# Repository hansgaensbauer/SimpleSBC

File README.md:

# SimpleSBC
A simple, open source SBC built around the STM32MP1

## Getting Started
1. `git clone` this repository
2. Run `git submodule init` and `git submodule update --recursive` to get Yocto and layers
3. Install dependencies:
   ```
   sudo apt update
   sudo apt upgrade
   sudo apt install -y bc build-essential chrpath cpio diffstat gawk git texinfo wget gdisk python3 python3-pip
   ```
4. Run `source yocto/poky/oe-init-build-env build-simplesbc` to set up the environment
5. Run `bitbake custom-image` to build! This could take a while
6. After the build, use yocto\copy_sd.sh to set up an SD card. You may need to change the device name in the script.
7. Connect an ST-Link or other USB-Serial converter, and plug in power.
8. Enjoy linux! The default meta-custom layer includes python and some python libraries. 

## Related Projects
- [Linux-Keyer](https://github.com/hansgaensbauer/Linux-Keyer/tree/main): A real-time linux based CW keyer built around SimpleSBC

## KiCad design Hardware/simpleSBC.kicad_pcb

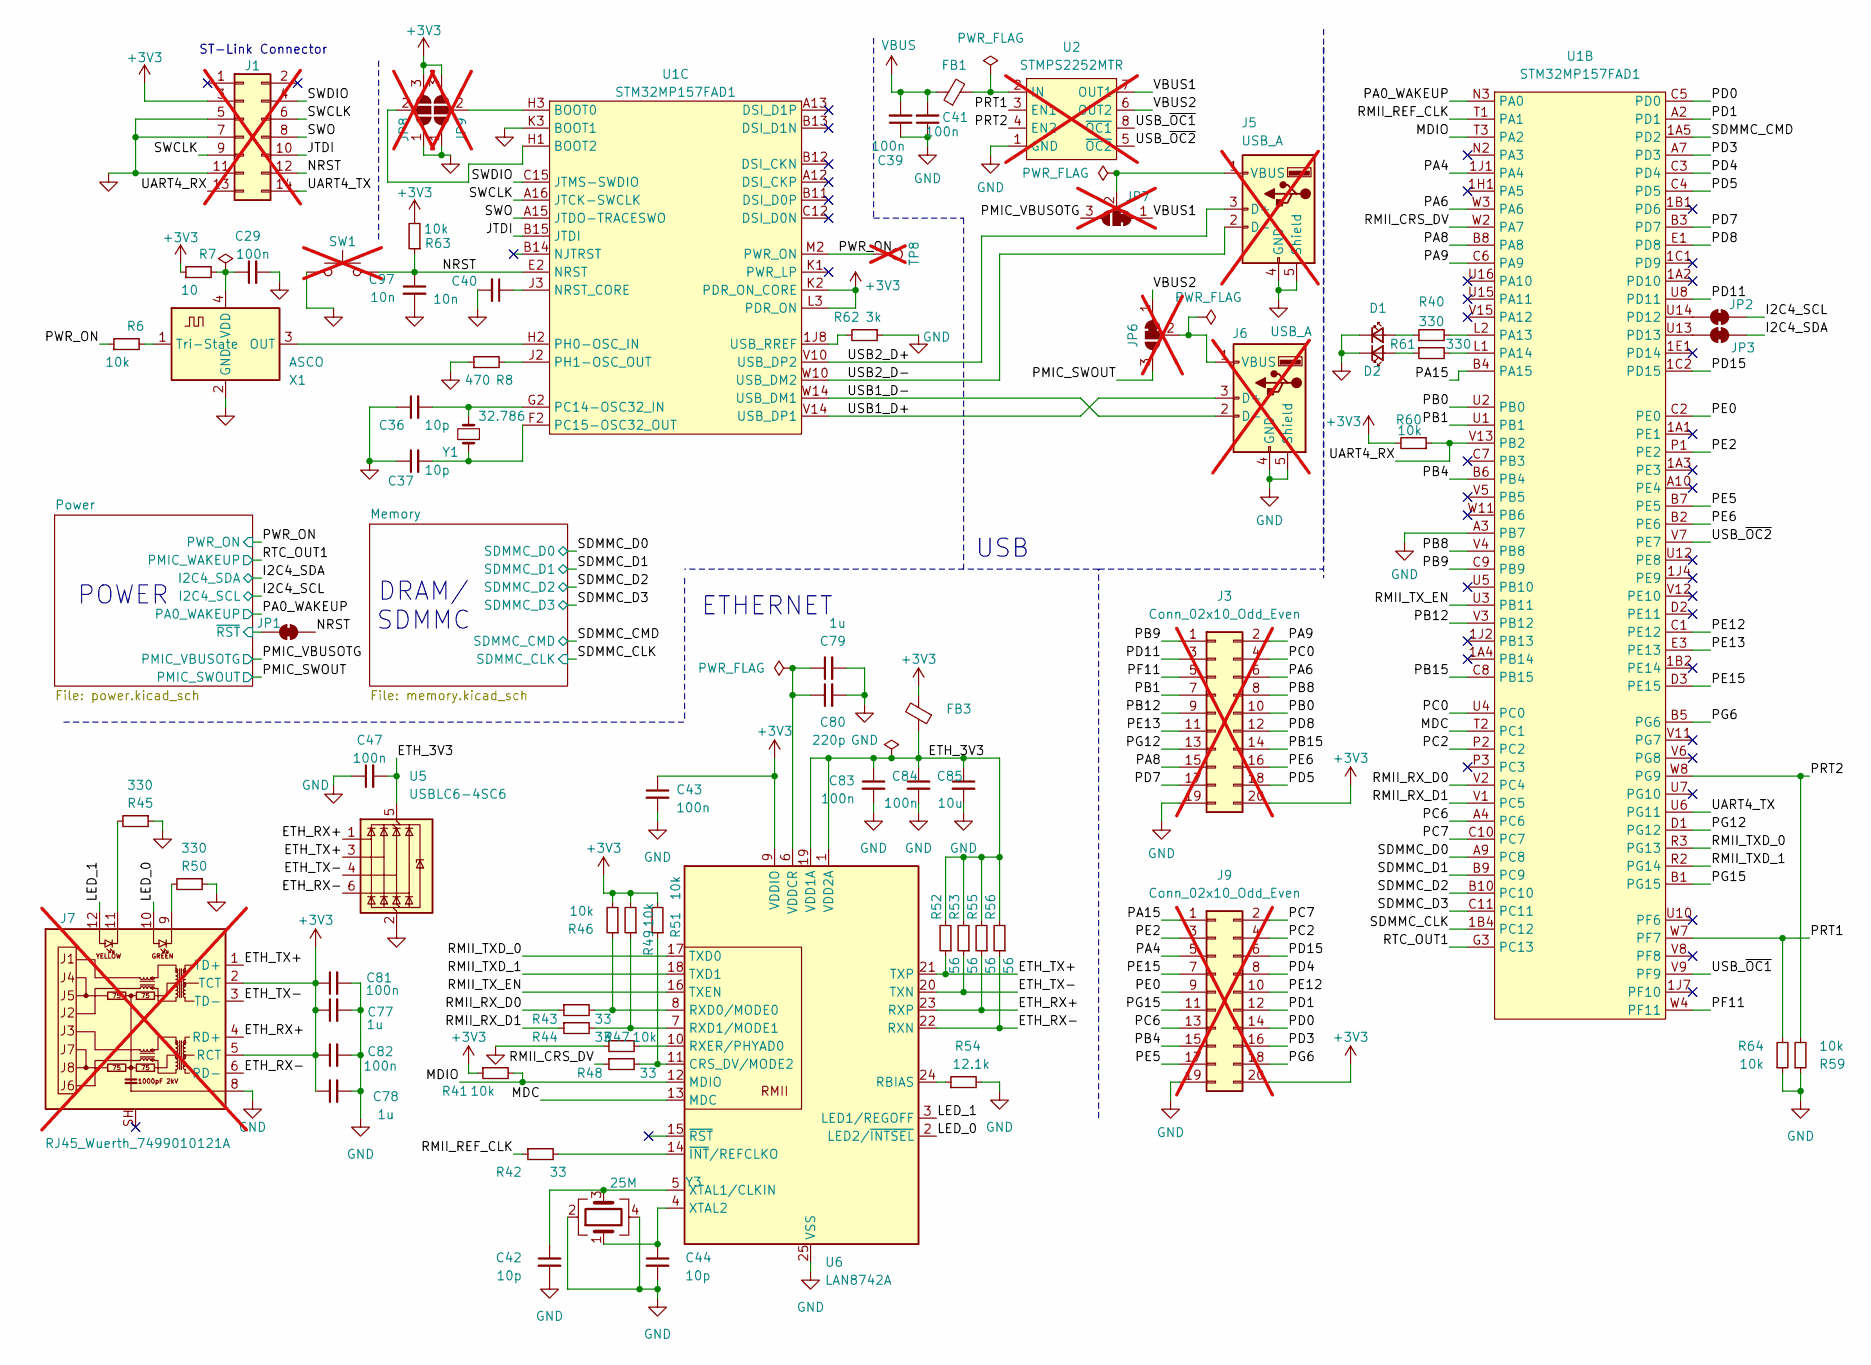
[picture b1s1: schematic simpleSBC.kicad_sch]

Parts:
C29, C39, C41, C43, C47, C81, C82, C83, C84: 100n; C_0402_1005Metric; JLCPCB Part # C1525
C36, C37, C42, C44: 10p; C_0402_1005Metric; JLCPCB Part # C32949
C40, C97: 10n; C_0402_1005Metric; JLCPCB Part # C15195
C77, C78, C79: 1u; C_0402_1005Metric; JLCPCB Part # C52923
C80: 220p; C_0402_1005Metric; JLCPCB Part # C1530
C85: 10u; C_0805_2012Metric; JLCPCB Part # C15850
D1: LED_Small; LED_0805_2012Metric; JLCPCB Part # C2296
D2: LED_Small; LED_0805_2012Metric; JLCPCB Part # C2297
FB1, FB3: FerriteBead_Small; L_0603_1608Metric; JLCPCB Part # C1002
J1: Conn_02x07_Odd_Even; PinHeader_2x7_P1.27mm_SMD; not fitted
J3, J9: Conn_02x10_Odd_Even; PinHeader_2x10_P2.54mm_Vertical; not fitted
J5, J6: USB_A; USB_A_Molex_67643_Horizontal; not fitted
J7: RJ45_Wuerth_7499010121A; RJ45_Wuerth_7499010121A_Horizontal; not fitted
JP1, JP2, JP3: SolderJumper_2_Bridged; Jumper_0402_Short
JP6, JP7: SolderJumper_3_Bridged12; SolderJumper-3_P1.3mm_Bridged2Bar12_Pad1.0x1.5mm; not fitted
JP8, JP9: SolderJumper_3_Open; SolderJumper-3_P1.3mm_Open_Pad1.0x1.5mm; not fitted
R6, R41, R46, R47, R49, R51, R59, R60, R63, R64: 10k; R_0402_1005Metric; JLCPCB Part # C25744
R7: 10; R_0402_1005Metric; JLCPCB Part # C25077
R8: 470; R_0402_1005Metric; JLCPCB Part # C25117
R40, R45, R50, R61: 330; R_0402_1005Metric; JLCPCB Part # C25104
R42, R43, R44, R48: 33; R_0402_1005Metric; JLCPCB Part # C25105
R52, R53, R55, R56: 56; R_0402_1005Metric; JLCPCB Part # C25127
R54: 12.1k; R_0402_1005Metric; JLCPCB Part # C25863
R62: 3k; R_0402_1005Metric; JLCPCB Part # C881171
SW1: SW_Push; SW_SPST_Omron_B3FS-101xP; not fitted
TP8: TestPoint; TestPoint_Pad_D1.0mm; not fitted
U1: STM32MP157FAD1; TFBGA257; JLCPCB Part # C1236719
U2: STMPS2252MTR; SOIC-8_3.9x4.9mm_P1.27mm; JLCPCB Part # C2680426; not fitted
U5: USBLC6-4SC6; SOT-23-6; JLCPCB Part # C111212
U6: LAN8742A; VQFN-24-1EP_4x4mm_P0.5mm_EP2.5x2.5mm_ThermalVias; JLCPCB Part # C220794
X1: ASCO; Oscillator_SMD_Abracon_ASCO-4Pin_1.6x1.2mm; JLCPCB Part # C19078199
Y1: 32.786; Crystal_SMD_MicroCrystal_CM9V-T1A-2Pin_1.6x1.0mm; JLCPCB Part # C5341287
Y3: 25M; Crystal_2.00x1.60mm; MPN 402F2501XIAR; JLCPCB Part # C127895

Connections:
+3V3: C43.1, C77.1, C78.1, C81.1, C82.1, FB3.2, J1.3, J3.20, J7.2 (TCT), J7.5 (RCT), J9.20, JP8.3 (B), JP9.3 (B), R7.1, R41.1, R46.2, R49.2, R51.2, R60.2, R63.2, U1.K2 (PDR_ON_CORE), U1.L3 (PDR_ON), U6.9 (VDDIO); also elsewhere on the board
/ETH_3V3: C47.2, C83.1, C84.1, C85.1, FB3.1, R52.2, R53.2, R55.2, R56.2, U5.5 (VBUS), U6.1 (VDD2A), U6.19 (VDD1A)
/ETH_RX+: J7.4 (RD+), R55.1, U5.1 (I/O1), U6.23 (RXP)
/ETH_RX-: J7.6 (RD-), R56.1, U5.6 (I/O4), U6.22 (RXN)
/ETH_TX+: J7.1 (TD+), R52.1, U5.3 (I/O2), U6.21 (TXP)
/ETH_TX-: J7.3 (TD-), R53.1, U5.4 (I/O3), U6.20 (TXN)
/I2C4_SCL: JP2.2 (B); also elsewhere on the board
/I2C4_SDA: JP3.2 (B); also elsewhere on the board
/JTDI: J1.10, U1.B15 (JTDI)
/LED_0: J7.10, U6.2 (LED2/~INTSEL)
/LED_1: J7.12, U6.3 (LED1/REGOFF)
/MDC: U1.T2 (PC1), U6.13 (MDC)
/MDIO: R41.2, U1.T3 (PA2), U6.12 (MDIO)
/NRST: C97.1, J1.12, JP1.2 (B), R63.1, SW1.2, U1.E2 (NRST)
/PA0_WAKEUP: U1.N3 (PA0); also elsewhere on the board
/PA4: J9.5, U1.1J1 (PA4)
/PA6: J3.6, U1.W3 (PA6)
/PA8: J3.15, U1.B8 (PA8)
/PA9: J3.2, U1.C6 (PA9)
/PA15: J9.1, U1.B4 (PA15)
/PB0: J3.10, U1.U2 (PB0)
/PB1: J3.7, U1.U1 (PB1)
/PB4: J9.15, U1.B6 (PB4)
/PB8: J3.8, U1.V4 (PB8)
/PB9: J3.1, U1.C9 (PB9)
/PB12: J3.9, U1.V3 (PB12)
/PB15: J3.14, U1.C8 (PB15)
/PC0: J3.4, U1.U4 (PC0)
/PC2: J9.4, U1.P2 (PC2)
/PC6: J9.13, U1.A4 (PC6)
/PC7: J9.2, U1.C10 (PC7)
/PD0: J9.14, U1.C5 (PD0)
/PD1: J9.12, U1.A2 (PD1)
/PD3: J9.16, U1.A7 (PD3)
/PD4: J9.8, U1.C3 (PD4)
/PD5: J3.18, U1.C4 (PD5)
/PD7: J3.17, U1.B3 (PD7)
/PD8: J3.12, U1.E1 (PD8)
/PD11: J3.3, U1.U8 (PD11)
/PD15: J9.6, U1.1C2 (PD15)
/PE0: J9.9, U1.C2 (PE0)
/PE2: J9.3, U1.P1 (PE2)
/PE5: J9.17, U1.B7 (PE5)
/PE6: J3.16, U1.B2 (PE6)
/PE12: J9.10, U1.C1 (PE12)
/PE13: J3.11, U1.E3 (PE13)
/PE15: J9.7, U1.D3 (PE15)
/PF11: J3.5, U1.W4 (PF11)
/PG6: J9.18, U1.B5 (PG6)
/PG12: J3.13, U1.D1 (PG12)
/PG15: J9.11, U1.B1 (PG15)
/PMIC_SWOUT: JP6.3 (B); also elsewhere on the board
/PMIC_VBUSOTG: JP7.3 (B); also elsewhere on the board
/PRT1: R64.2, U1.W7 (PF7), U2.3 (EN1)
/PRT2: R59.2, U1.W8 (PG9), U2.4 (EN2)
/PWR_ON: R6.1, TP8.1, U1.M2 (PWR_ON); also elsewhere on the board
/Power/~RST: JP1.1 (A); also elsewhere on the board
/RMII_CRS_DV: R48.1, U1.W2 (PA7)
/RMII_REF_CLK: R42.1, U1.T1 (PA1)
/RMII_RX_D0: R43.1, U1.V2 (PC4)
/RMII_RX_D1: R44.1, U1.V1 (PC5)
/RMII_TXD_0: U1.R3 (PG13), U6.17 (TXD0)
/RMII_TXD_1: U1.R2 (PG14), U6.18 (TXD1)
/RMII_TX_EN: U1.U3 (PB11), U6.16 (TXEN)
/RTC_OUT1: U1.G3 (PC13); also elsewhere on the board
/SDMMC_CLK: U1.1B4 (PC12); also elsewhere on the board
/SDMMC_CMD: U1.1A5 (PD2); also elsewhere on the board
/SDMMC_D0: U1.A9 (PC8); also elsewhere on the board
/SDMMC_D1: U1.B9 (PC9); also elsewhere on the board
/SDMMC_D2: U1.B10 (PC10); also elsewhere on the board
/SDMMC_D3: U1.C11; also elsewhere on the board
/SWCLK: J1.6, J1.9, U1.A16 (JTCK-SWCLK)
/SWDIO: J1.4, U1.C15 (JTMS-SWDIO)
/SWO: J1.8, U1.A15 (JTDO-TRACESWO)
/UART4_RX: J1.13, R60.1, U1.V13 (PB2)
/UART4_TX: J1.14, U1.U6 (PG11)
/USB1_D+: J6.3 (D+), U1.V14 (USB_DP1)
/USB1_D-: J6.2 (D-), U1.W14 (USB_DM1)
/USB2_D+: J5.3 (D+), U1.V10 (USB_DP2)
/USB2_D-: J5.2 (D-), U1.W10 (USB_DM2)
/USB_~OC1: U1.V9 (PF9), U2.8 (~OC1)
/USB_~OC2: U1.V7 (PE7), U2.5 (~OC2)
/VBUS1: JP7.1 (A), U2.7 (OUT1)
/VBUS2: JP6.1 (A), U2.6 (OUT2)
GND: C29.2, C36.1, C37.1, C39.1, C40.2, C41.1, C42.2, C43.2, C44.2, C47.1, C77.2, C78.2, C79.2, C80.2, C81.2, C82.2, C83.2, C84.2, C85.2, C97.2, D1.1 (K), D2.1 (K), J1.5, J1.7, J1.11, J3.19, J5.4 (GND), J5.5 (Shield), J6.4 (GND), J6.5 (Shield), J7.8, J9.19, JP8.1 (A), JP9.1 (A), R8.1, R45.1, R47.1, R50.1, R54.2, R59.1, R62.1, R64.1, SW1.1, U1.A3 (PB7), U1.K3 (BOOT1), U2.1 (GND), U5.2 (GND), U6.25 (VSS), X1.2 (GND), Y3.2, Y3.4; also elsewhere on the board
unnamed: D1.2 (A), R40.1
unnamed: D2.2 (A), R61.1
unnamed: J5.1 (VBUS), JP7.2 (C)
unnamed: J6.1 (VBUS), JP6.2 (C)
unnamed: J7.9, R50.2
unnamed: J7.11, R45.2
unnamed: JP2.1 (A), U1.U14 (PD12)
unnamed: JP3.1 (A), U1.U13 (PD13)
unnamed: JP8.2 (C), U1.H1 (BOOT2)
unnamed: JP9.2 (C), U1.H3 (BOOT0)
unnamed: R40.2, U1.L2 (PA13)
unnamed: R61.2, U1.L1 (PA14)
unnamed: C40.1, U1.J3 (NRST_CORE)
unnamed: C36.2, U1.G2 (PC14-OSC32_IN), Y1.2
unnamed: C37.2, U1.F2 (PC15-OSC32_OUT), Y1.1
unnamed: U1.H2 (PH0-OSC_IN), X1.3 (OUT)
unnamed: R8.2, U1.J2 (PH1-OSC_OUT)
unnamed: R62.2, U1.1J8 (USB_RREF)
unnamed: FB1.2, U2.2 (IN)
unnamed: R48.2, R51.1, U6.11 (CRS_DV/MODE2)
unnamed: R54.1, U6.24 (RBIAS)
unnamed: R43.2, R46.1, U6.8 (RXD0/MODE0)
unnamed: R44.2, R49.1, U6.7 (RXD1/MODE1)
unnamed: R47.2, U6.10 (RXER/PHYAD0)
unnamed: C79.1, C80.1, U6.6 (VDDCR)
unnamed: C42.1, U6.5 (XTAL1/CLKIN), Y3.3
unnamed: C44.1, U6.4 (XTAL2), Y3.1
unnamed: R42.2, U6.14 (~INT/REFCLKO)
unnamed: R6.2, X1.1 (Tri-State)
unnamed: C29.1, R7.2, X1.4 (VDD)
VBUS: C39.2, C41.2, FB1.1; also elsewhere on the board

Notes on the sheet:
USB
DRAM/ SDMMC
POWER
ETHERNET
ST-Link Connector

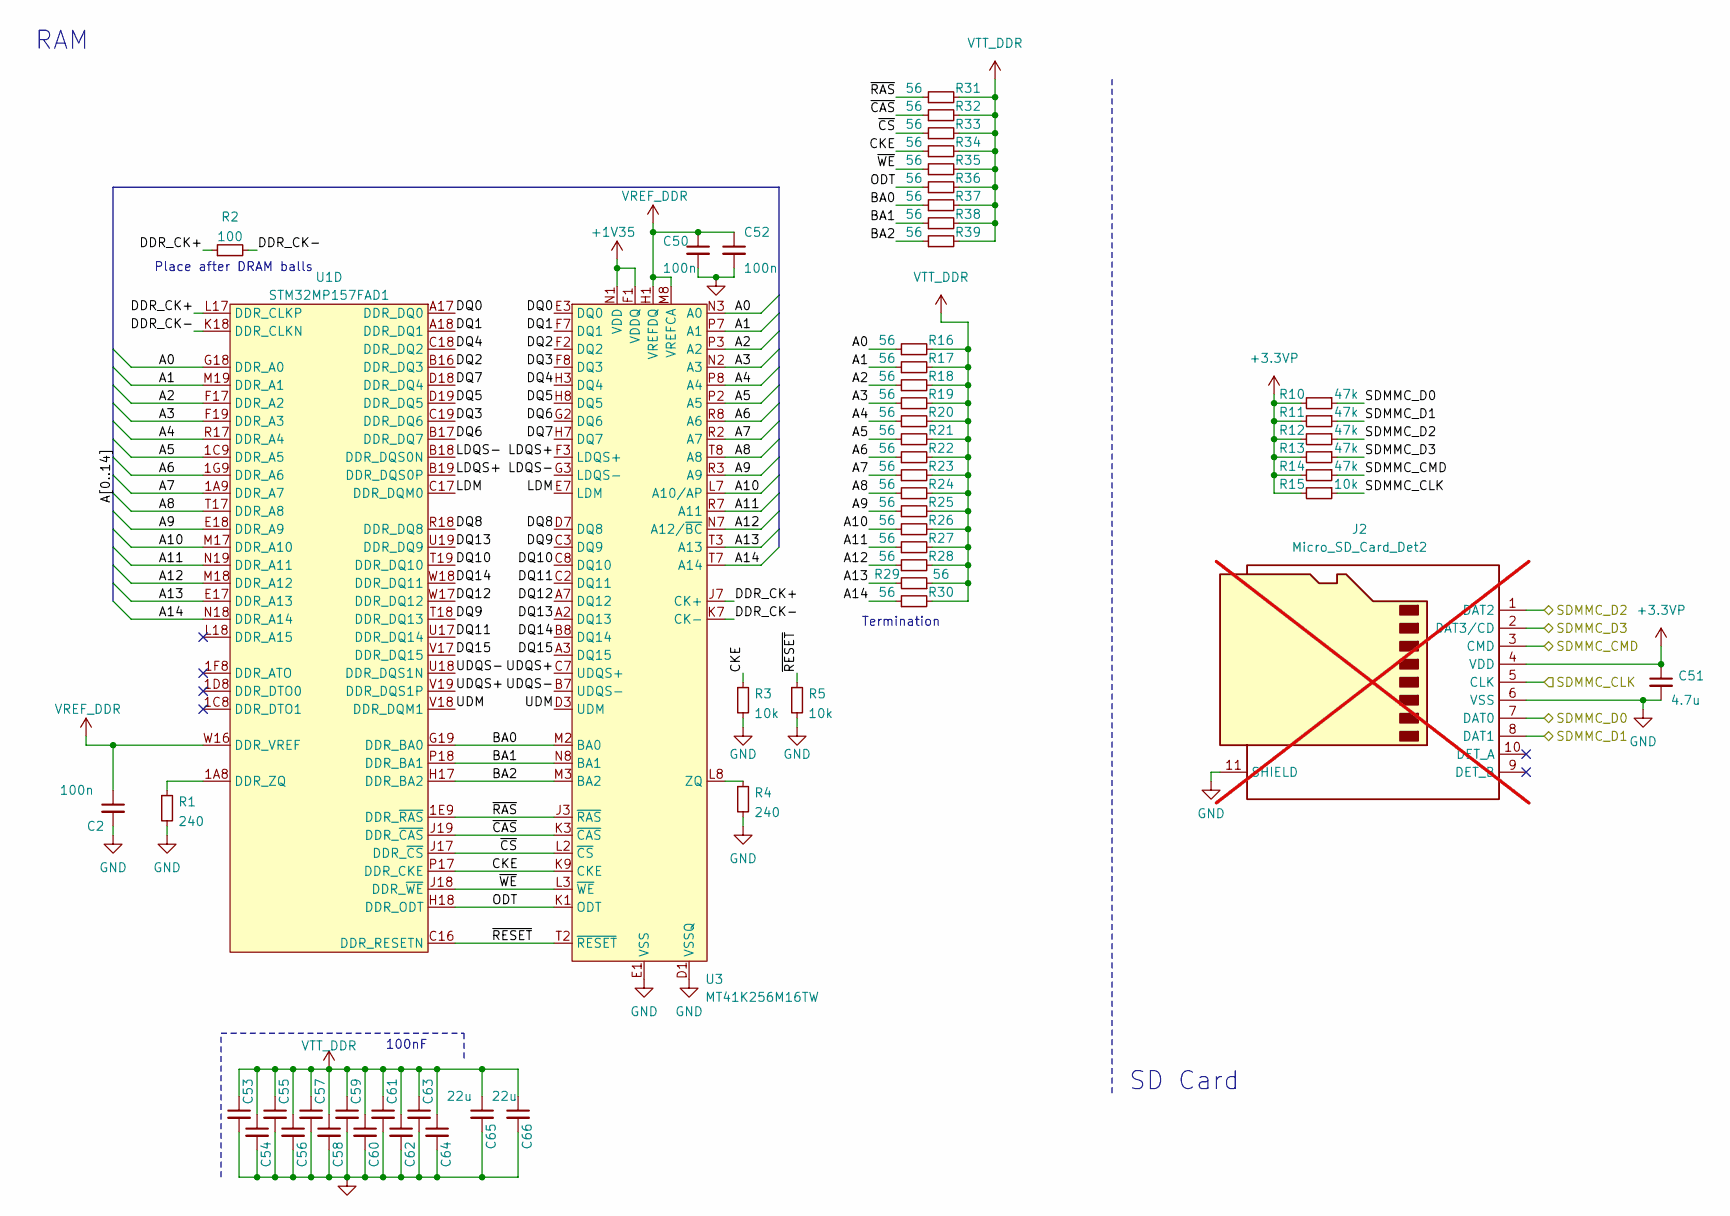
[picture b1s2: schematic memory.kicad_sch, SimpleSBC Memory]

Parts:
C2, C50, C52, C53, C54, C55, C56, C57, C58, C59, C60, C61, C62, C63, C64: 100n; C_0402_1005Metric; JLCPCB Part # C1525
C51: 4.7u; C_0402_1005Metric; JLCPCB Part # C23733
C65, C66: 22u; C_0805_2012Metric; JLCPCB Part # C45783
J2: Micro_SD_Card_Det2; microSD_HC_Molex_104031-0811; not fitted
R1, R4: 240; R_0402_1005Metric; JLCPCB Part # C208835
R2: 100; R_0402_1005Metric; JLCPCB Part # C25076
R3, R5, R15: 10k; R_0402_1005Metric; JLCPCB Part # C25744
R10, R11, R12, R13, R14: 47k; R_0402_1005Metric; JLCPCB Part # C25792
R16, R17, R18, R19, R20, R21, R22, R23, R24, R25, R26, R27, R28, R29, R30, R31, R32, R33, R34, R35, R36, R37, R38, R39: 56; R_0402_1005Metric; JLCPCB Part # C25127
U1: STM32MP157FAD1; TFBGA257; JLCPCB Part # C1236719
U3: MT41K256M16TW; BGA-96_9.0x13.0mm_Layout2x3x16_P0.8mm; JLCPCB Part # C253882

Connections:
+1V35: U3.A1 (VDDQ), U3.A8 (VDDQ), U3.B2 (VDD), U3.C1 (VDDQ), U3.C9 (VDDQ), U3.D2 (VDDQ), U3.D9 (VDD), U3.E9 (VDDQ), U3.F1 (VDDQ), U3.G7 (VDD), U3.H2 (VDDQ), U3.H9 (VDDQ), U3.K2 (VDD), U3.K8 (VDD), U3.N1 (VDD), U3.N9 (VDD), U3.R1 (VDD), U3.R9 (VDD); also elsewhere on the board
+3.3VP: C51.1, J2.4 (VDD), R10.2, R11.2, R12.2, R13.2, R14.2, R15.2; also elsewhere on the board
/Memory/A0: R16.1, U1.G18 (DDR_A0), U3.N3 (A0)
/Memory/A1: R17.1, U1.M19 (DDR_A1), U3.P7 (A1)
/Memory/A2: R18.1, U1.F17 (DDR_A2), U3.P3 (A2)
/Memory/A3: R19.1, U1.F19 (DDR_A3), U3.N2 (A3)
/Memory/A4: R20.1, U1.R17 (DDR_A4), U3.P8 (A4)
/Memory/A5: R21.1, U1.1C9 (DDR_A5), U3.P2 (A5)
/Memory/A6: R22.1, U1.1G9 (DDR_A6), U3.R8 (A6)
/Memory/A7: R23.1, U1.1A9 (DDR_A7), U3.R2 (A7)
/Memory/A8: R24.1, U1.T17 (DDR_A8), U3.T8 (A8)
/Memory/A9: R25.1, U1.E18 (DDR_A9), U3.R3 (A9)
/Memory/A10: R26.1, U1.M17 (DDR_A10), U3.L7 (A10/AP)
/Memory/A11: R27.1, U1.N19 (DDR_A11), U3.R7 (A11)
/Memory/A12: R28.1, U1.M18 (DDR_A12), U3.N7 (A12/~BC)
/Memory/A13: R29.2, U1.E17 (DDR_A13), U3.T3 (A13)
/Memory/A14: R30.1, U1.N18 (DDR_A14), U3.T7 (A14)
/Memory/BA0: R37.1, U1.G19 (DDR_BA0), U3.M2 (BA0)
/Memory/BA1: R38.1, U1.P18 (DDR_BA1), U3.N8 (BA1)
/Memory/BA2: R39.1, U1.H17 (DDR_BA2), U3.M3 (BA2)
/Memory/CKE: R3.1, R34.1, U1.P17 (DDR_CKE), U3.K9 (CKE)
/Memory/DDR_CK+: R2.1, U1.L17 (DDR_CLKP), U3.J7 (CK+)
/Memory/DDR_CK-: R2.2, U1.K18 (DDR_CLKN), U3.K7 (CK-)
/Memory/DQ0: U1.A17 (DDR_DQ0), U3.E3 (DQ0)
/Memory/DQ1: U1.A18 (DDR_DQ1), U3.F7 (DQ1)
/Memory/DQ2: U1.B16 (DDR_DQ3), U3.F2 (DQ2)
/Memory/DQ3: U1.C19 (DDR_DQ6), U3.F8 (DQ3)
/Memory/DQ4: U1.C18 (DDR_DQ2), U3.H3 (DQ4)
/Memory/DQ5: U1.D19 (DDR_DQ5), U3.H8 (DQ5)
/Memory/DQ6: U1.B17 (DDR_DQ7), U3.G2 (DQ6)
/Memory/DQ7: U1.D18 (DDR_DQ4), U3.H7 (DQ7)
/Memory/DQ8: U1.R18 (DDR_DQ8), U3.D7 (DQ8)
/Memory/DQ9: U1.T18 (DDR_DQ13), U3.C3 (DQ9)
/Memory/DQ10: U1.T19 (DDR_DQ10), U3.C8 (DQ10)
/Memory/DQ11: U1.U17 (DDR_DQ14), U3.C2 (DQ11)
/Memory/DQ12: U1.W17 (DDR_DQ12), U3.A7 (DQ12)
/Memory/DQ13: U1.U19 (DDR_DQ9), U3.A2 (DQ13)
/Memory/DQ14: U1.W18 (DDR_DQ11), U3.B8 (DQ14)
/Memory/DQ15: U1.V17 (DDR_DQ15), U3.A3 (DQ15)
/Memory/LDM: U1.C17 (DDR_DQM0), U3.E7 (LDM)
/Memory/LDQS+: U1.B19 (DDR_DQS0P), U3.F3 (LDQS+)
/Memory/LDQS-: U1.B18 (DDR_DQS0N), U3.G3 (LDQS-)
/Memory/ODT: R36.1, U1.H18 (DDR_ODT), U3.K1 (ODT)
/Memory/UDM: U1.V18 (DDR_DQM1), U3.D3 (UDM)
/Memory/UDQS+: U1.V19 (DDR_DQS1P), U3.C7 (UDQS+)
/Memory/UDQS-: U1.U18 (DDR_DQS1N), U3.B7 (UDQS-)
/Memory/~CAS: R32.1, U1.J19 (DDR_~CAS), U3.K3 (~CAS)
/Memory/~CS: R33.1, U1.J17 (DDR_~CS), U3.L2 (~CS)
/Memory/~RAS: R31.1, U1.1E9 (DDR_~RAS), U3.J3 (~RAS)
/Memory/~RESET: R5.1, U1.C16 (DDR_RESETN), U3.T2 (~RESET)
/Memory/~WE: R35.1, U1.J18 (DDR_~WE), U3.L3 (~WE)
/SDMMC_CLK: J2.5 (CLK), R15.1; also elsewhere on the board
/SDMMC_CMD: J2.3 (CMD), R14.1; also elsewhere on the board
/SDMMC_D0: J2.7 (DAT0), R10.1; also elsewhere on the board
/SDMMC_D1: J2.8 (DAT1), R11.1; also elsewhere on the board
/SDMMC_D2: J2.1 (DAT2), R12.1; also elsewhere on the board
/SDMMC_D3: J2.2 (DAT3/CD), R13.1; also elsewhere on the board
GND: C2.2, C50.2, C51.2, C52.2, C53.2, C54.2, C55.2, C56.2, C57.2, C58.2, C59.2, C60.2, C61.2, C62.2, C63.2, C64.2, C65.2, C66.2, J2.6 (VSS), J2.11 (SHIELD), R1.2, R3.2, R4.2, R5.2, U3.A9 (VSS), U3.B1 (VSSQ), U3.B3 (VSS), U3.B9 (VSSQ), U3.D1 (VSSQ), U3.D8 (VSSQ), U3.E1 (VSS), U3.E2 (VSSQ), U3.E8 (VSSQ), U3.F9 (VSSQ), U3.G1 (VSSQ), U3.G8 (VSS), U3.G9 (VSSQ), U3.J2 (VSS), U3.J8 (VSS), U3.M1 (VSS), U3.M9 (VSS), U3.P1 (VSS), U3.P9 (VSS), U3.T1 (VSS), U3.T9 (VSS); also elsewhere on the board
unnamed: R1.1, U1.1A8 (DDR_ZQ)
unnamed: R4.1, U3.L8 (ZQ)
VREF_DDR: C2.1, C50.1, C52.1, U1.W16 (DDR_VREF), U3.H1 (VREFDQ), U3.M8 (VREFCA); also elsewhere on the board
VTT_DDR: C53.1, C54.1, C55.1, C56.1, C57.1, C58.1, C59.1, C60.1, C61.1, C62.1, C63.1, C64.1, C65.1, C66.1, R16.2, R17.2, R18.2, R19.2, R20.2, R21.2, R22.2, R23.2, R24.2, R25.2, R26.2, R27.2, R28.2, R29.1, R30.2, R31.2, R32.2, R33.2, R34.2, R35.2, R36.2, R37.2, R38.2, R39.2; also elsewhere on the board

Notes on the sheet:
RAM
SD Card
100nF
Place after DRAM balls
Termination

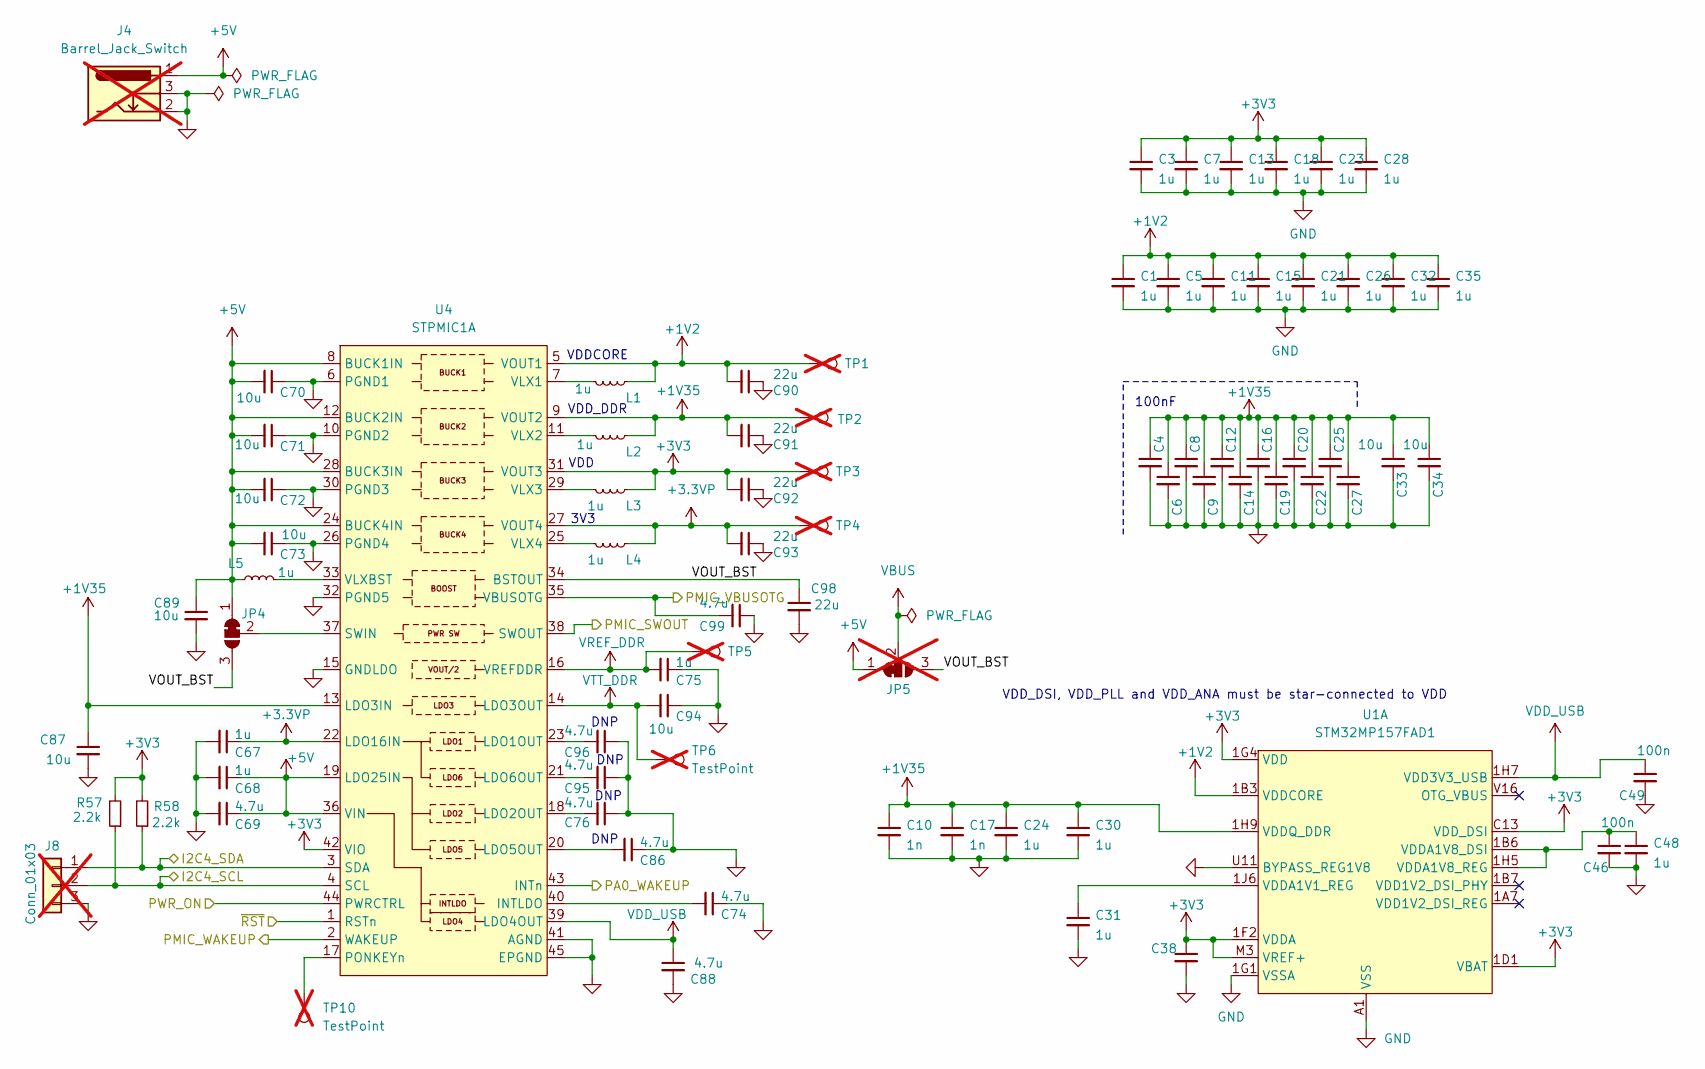
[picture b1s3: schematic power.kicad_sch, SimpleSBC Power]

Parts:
C1, C3, C5, C7, C11, C13, C15, C18, C21, C23, C24, C26, C28, C30, C31, C32, C35, C38, C48, C67, C68, C75: 1u; C_0402_1005Metric; JLCPCB Part # C52923
C4, C6, C8, C9, C12, C14, C16, C19, C20, C22, C25, C27, C46, C49: 100n; C_0402_1005Metric; JLCPCB Part # C1525
C10, C17: 1n; C_0402_1005Metric; JLCPCB Part # C1523
C33, C34: 10u; C_0805_2012Metric; JLCPCB Part # C15850
C69, C74, C76, C86, C88, C95, C96, C99: 4.7u; C_0402_1005Metric; JLCPCB Part # C23733
C70, C71, C72, C73, C87, C89, C94: 10u; C_0603_1608Metric; JLCPCB Part # C19702
C90, C91, C92, C93, C98: 22u; C_0805_2012Metric; JLCPCB Part # C45783
J4: Barrel_Jack_Switch; BarrelJack_Wuerth_6941xx301002; not fitted
J8: Conn_01x03; PinHeader_1x03_P2.54mm_Vertical; not fitted
JP4: SolderJumper_3_Bridged12; SolderJumper-3_P1.3mm_Bridged2Bar12_Pad1.0x1.5mm
JP5: SolderJumper_3_Bridged12; SolderJumper-3_P1.3mm_Bridged2Bar12_Pad1.0x1.5mm; not fitted
L1, L2, L3, L4, L5: 1u; L_1008_2520Metric; JLCPCB Part # C76795
R57, R58: 2.2k; R_0402_1005Metric; JLCPCB Part # C25879
TP1, TP2, TP3, TP4, TP5, TP6, TP10: TestPoint; TestPoint_Pad_D1.0mm; not fitted
U1: STM32MP157FAD1; TFBGA257; JLCPCB Part # C1236719
U4: STPMIC1A; WFQFN44L; JLCPCB Part # C2156050

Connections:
+1V2: C1.1, C5.1, C11.1, C15.1, C21.1, C26.1, C32.1, C35.1, C90.2, L1.2, TP1.1, U1.1B3 (VDDCORE), U1.1B5 (VDDCORE), U1.1C4 (VDDCORE), U1.1C6 (VDDCORE), U1.1D3 (VDDCORE), U1.1D5 (VDDCORE), U1.1D7 (VDDCORE), U1.1E4 (VDDCORE), U1.1E6 (VDDCORE), U1.1E8 (VDDCORE), U1.1F5 (VDDCORE), U1.1F7 (VDDCORE), U1.1G6 (VDDCORE), U1.1G8 (VDDCORE), U4.5 (VOUT1)
+1V35: C4.1, C6.1, C8.1, C9.1, C10.1, C12.1, C14.1, C16.1, C17.1, C19.1, C20.1, C22.1, C24.1, C25.1, C27.1, C30.1, C33.1, C34.1, C87.1, C91.2, L2.2, TP2.1, U1.1B9 (VDDQ_DDR), U1.1D9 (VDDQ_DDR), U1.1F9 (VDDQ_DDR), U1.1H9 (VDDQ_DDR), U4.9 (VOUT2), U4.13 (LDO3IN); also elsewhere on the board
+3.3VP: C67.1, C93.2, L4.2, TP4.1, U4.22 (LDO16IN), U4.27 (VOUT4); also elsewhere on the board
+3V3: C3.1, C7.1, C13.1, C18.1, C23.1, C28.1, C38.1, C92.2, L3.2, R57.2, R58.2, TP3.1, U1.1D1 (VBAT), U1.1E2 (VDD), U1.1F1 (VDDA), U1.1F2 (VDDA), U1.1F3 (VDD), U1.1G3 (VDD), U1.1G4 (VDD), U1.1J3 (VDD), U1.C13 (VDD_DSI), U1.M3 (VREF+), U4.31 (VOUT3), U4.42 (VIO); also elsewhere on the board
+5V: C68.1, C69.1, C70.2, C71.2, C72.2, C73.2, C89.1, J4.1, JP4.1 (A), JP5.1 (A), L5.2, U4.8 (BUCK1IN), U4.12 (BUCK2IN), U4.19 (LDO25IN), U4.24 (BUCK4IN), U4.28 (BUCK3IN), U4.36 (VIN)
/I2C4_SCL: J8.2, R57.1, U4.4 (SCL); also elsewhere on the board
/I2C4_SDA: J8.1, R58.1, U4.3 (SDA); also elsewhere on the board
/PA0_WAKEUP: U4.43 (INTn); also elsewhere on the board
/PMIC_SWOUT: U4.38 (SWOUT); also elsewhere on the board
/PMIC_VBUSOTG: C99.2, U4.35 (VBUSOTG); also elsewhere on the board
/PWR_ON: U4.44 (PWRCTRL); also elsewhere on the board
/Power/VOUT_BST: C98.1, JP4.3 (B), JP5.3 (B), U4.34 (BSTOUT)
/Power/~RST: U4.1 (RSTn); also elsewhere on the board
/RTC_OUT1: U4.2 (WAKEUP); also elsewhere on the board
GND: C1.2, C3.2, C4.2, C5.2, C6.2, C7.2, C8.2, C9.2, C10.2, C11.2, C12.2, C13.2, C14.2, C15.2, C16.2, C17.2, C18.2, C19.2, C20.2, C21.2, C22.2, C23.2, C24.2, C25.2, C26.2, C27.2, C28.2, C30.2, C31.2, C32.2, C33.2, C34.2, C35.2, C38.2, C46.2, C48.2, C49.2, C67.2, C68.2, C69.2, C70.1, C71.1, C72.1, C73.1, C74.1, C75.1, C76.1, C86.1, C87.2, C88.2, C89.2, C90.1, C91.1, C92.1, C93.1, C94.1, C95.1, C96.1, C98.2, C99.1, J4.2, J4.3, J8.3, U1.1A6 (VSS), U1.1B8 (VSS), U1.1C3 (VSS), U1.1C5 (VSS), U1.1C7 (VSS), U1.1D2 (VSS), U1.1D4 (VSS), U1.1D6 (VSS), U1.1E3 (VSS), U1.1E5 (VSS), U1.1E7 (VSS), U1.1F4 (VSS), U1.1F6 (VSS), U1.1G1 (VSSA), U1.1G2 (VSS), U1.1G5 (VSS), U1.1G7 (VSS), U1.1H2 (VSS), U1.1H3 (VSS), U1.1H4 (VSS), U1.1H6 (VSS), U1.1H8 (VSS), U1.1J5 (VSS), U1.1J9 (VSS), U1.A1 (VSS), U1.A6 (VSS), U1.A19 (VSS), U1.C14 (VSS), U1.D17 (VSS), U1.F3 (VSS), U1.F18 (VSS), U1.G1 (VSS), U1.G17 (VSS), U1.K17 (VSS), U1.K19 (VSS), U1.N1 (VSS), U1.N17 (VSS), U1.R19 (VSS), U1.U9 (VSS), U1.U11 (BYPASS_REG1V8), U1.W1 (VSS), U1.W5 (VSS), U1.W13 (VSS), U1.W19 (VSS), U4.6 (PGND1), U4.10 (PGND2), U4.15 (GNDLDO), U4.26 (PGND4), U4.30 (PGND3), U4.32 (PGND5), U4.41 (AGND), U4.45 (EPGND); also elsewhere on the board
unnamed: JP4.2 (C), U4.37 (SWIN)
unnamed: C31.1, U1.1J6 (VDDA1V1_REG)
unnamed: C46.1, C48.1, U1.1B6 (VDDA1V8_DSI), U1.1H5 (VDDA1V8_REG)
unnamed: C74.2, U4.40 (INTLDO)
unnamed: C96.2, U4.23 (LDO1OUT)
unnamed: C76.2, U4.18 (LDO2OUT)
unnamed: C86.2, U4.20 (LDO5OUT)
unnamed: C95.2, U4.21 (LDO6OUT)
unnamed: TP10.1, U4.17 (PONKEYn)
unnamed: L1.1, U4.7 (VLX1)
unnamed: L2.1, U4.11 (VLX2)
unnamed: L3.1, U4.29 (VLX3)
unnamed: L4.1, U4.25 (VLX4)
unnamed: L5.1, U4.33 (VLXBST)
VBUS: JP5.2 (C); also elsewhere on the board
VDD_USB: C49.1, C88.1, U1.1H7 (VDD3V3_USB), U4.39 (LDO4OUT)
VREF_DDR: C75.2, TP5.1, U4.16 (VREFDDR); also elsewhere on the board
VTT_DDR: C94.2, TP6.1, U4.14 (LDO3OUT); also elsewhere on the board

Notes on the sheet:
VDD
DNP
VDDCORE
100nF
3V3
VDD_DDR
VDD_DSI, VDD_PLL and VDD_ANA must be star-connected to VDD

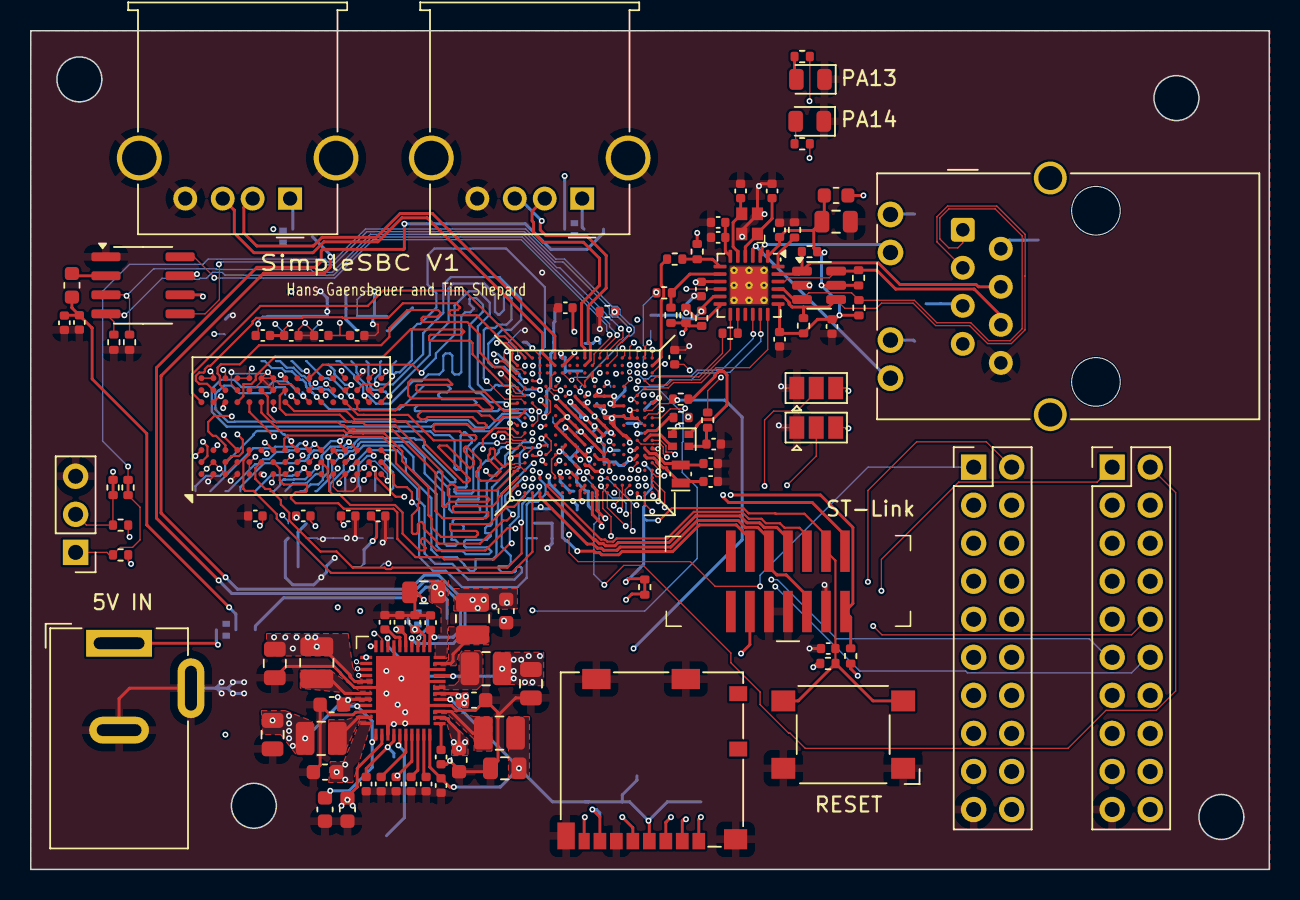
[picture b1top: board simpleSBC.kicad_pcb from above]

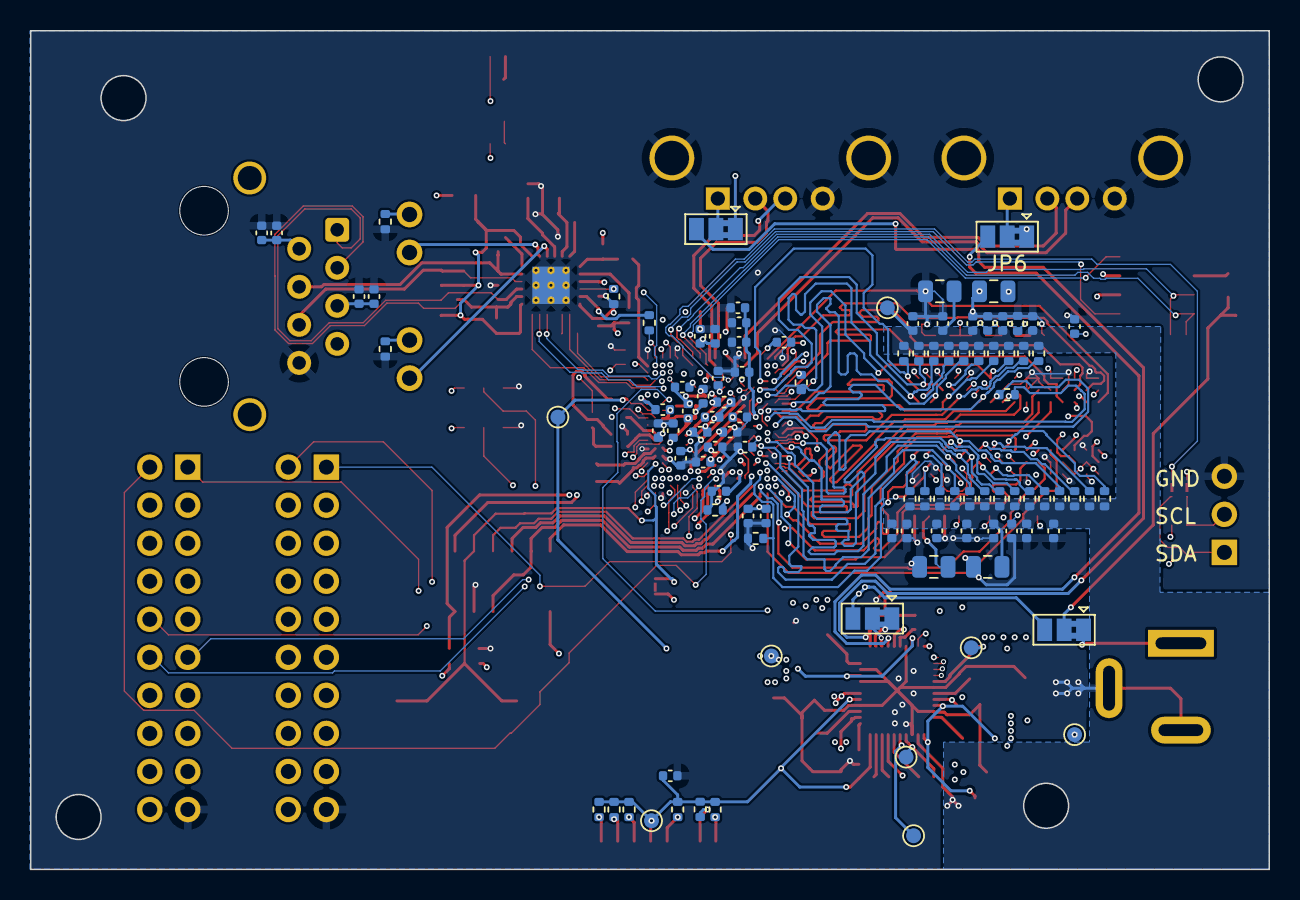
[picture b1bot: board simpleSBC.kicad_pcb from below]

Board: 6 copper layers, 82.7 x 56.0 mm, 206 parts (101 on the bottom side), 189 nets.

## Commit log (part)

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2022-06-21 Hardware: Add initial Hardware
2025-01-13 Add STPMIC1
2025-02-03 update gitignore
2025-02-03 Remove old files
2025-02-03 Remove prl
2025-02-03 Create libraries and move custom symbols to project specific libraries
2025-02-04 First Draft schematic (R2)
2025-02-05 Add Ethernet and USB power switching
2025-02-05 Schematic symbol pin type fixes
2025-02-07 First pass through ST Design Checklist
2025-02-09 First Pass for Floorplanning
2025-03-06 First Pass Routing
2025-03-09 ERC/DRC Clean
2025-03-23 Redo DRAM Length Tuning
2025-03-23 Reconnect Nets after length tuning
2025-03-23 Add Boot selection jumpers
2025-03-24 Add USB enable pulldowns
2025-03-24 Update .gitignore to remove cam
2025-03-25 prepare for assembly
2025-03-26 Default close jumpers and fix USB signal switching
2025-03-26 Don't track auto_saved_files
2025-07-01 Add photos and update readme
2025-07-09 Add yocto initially
2025-07-12 submodule configuration
2025-07-15 update to scarthgap
2025-07-16 Custom device tree modifications
2025-07-19 Boot with custom dts
2025-07-19 Fix root password
2025-07-19 Clean DSI from device tree
2025-07-19 Add python and libraries
2025-07-19 remove cryptography module
2025-07-19 remove references to eval board device trees
2025-07-19 remove eval kit files in optee
2025-07-25 Fix README.md spelling
2026-01-07 Update ethernet dt entries
2026-04-21 Stale changes
2026-05-23 Fix yocto submodule url and submodule issue in readme
2026-06-28 add kicad history to gitignore
2026-06-28 Fix bblayers.conf paths
